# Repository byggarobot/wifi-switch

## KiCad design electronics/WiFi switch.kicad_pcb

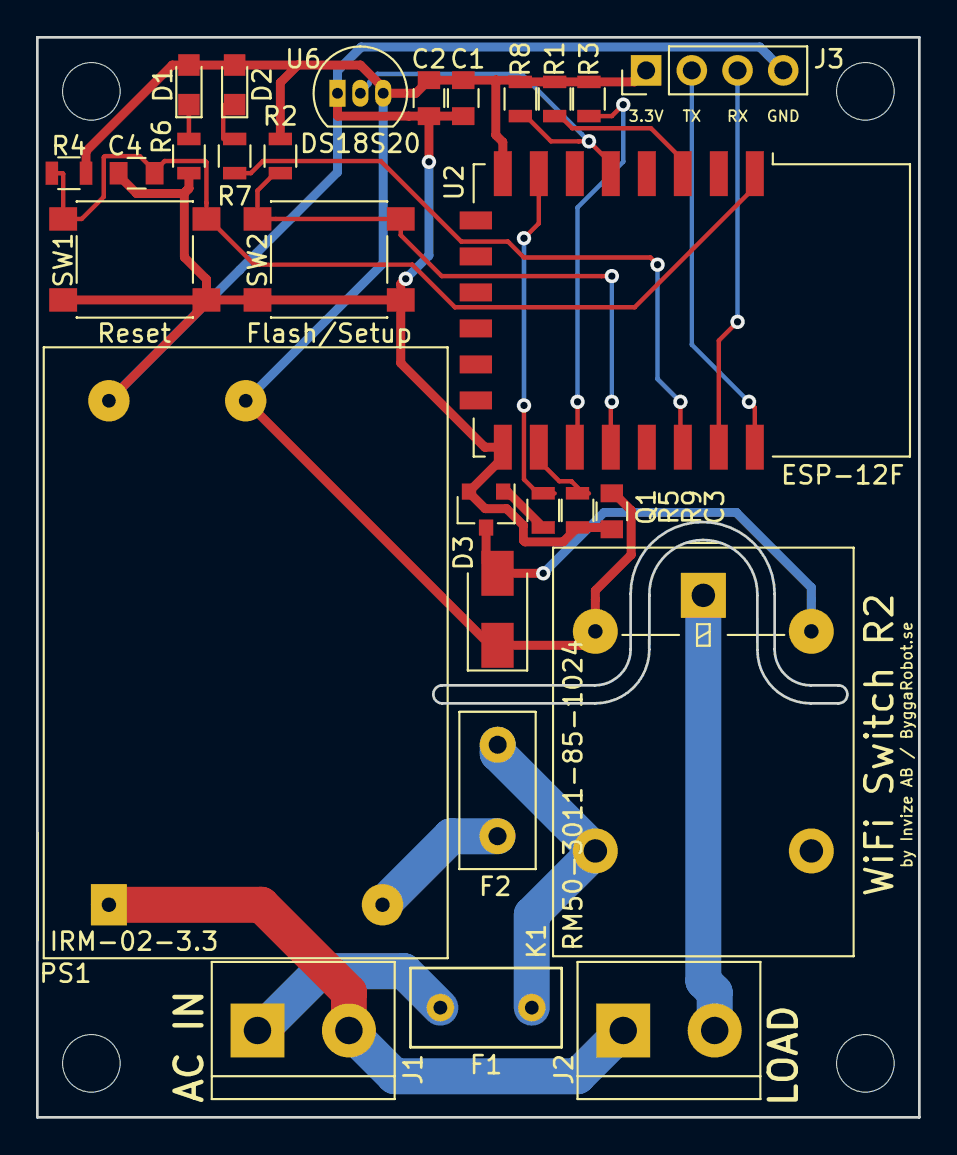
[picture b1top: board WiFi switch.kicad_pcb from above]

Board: 2 copper layers, 49.0 x 60.0 mm, 28 parts (0 on the bottom side), 21 nets.

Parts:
C1, C3: 10uF; C_0805
C2, C4: 100nF; C_0805
D1, D2: LED; LED_0805
D3: SS34; D_SMA
F1: 5A; RS Pro Non-resettable fuse
F2: 0.08A LVR008NK; Fuse_TE5_Littlefuse-395Series
J1: AC IN; TerminalBlock_bornier-2_P5.08mm
J2: LOAD; TerminalBlock_bornier-2_P5.08mm
J3: Programmer; Pin_Header_Straight_1x04_Pitch2.54mm
K1: RM50-3011-85-1024; Relay_SPDT_Relpol_RM50-3011-85-1024
PS1: IRM-02-3.3; ACDC-Conv_THTMeanWell-IRM-02-XX
Q1: BC817; SOT-23
R1, R2, R3, R4, R5, R6, R7: 10K; R_0805
R8: 4.7K; R_0805
R9: 1K; R_0805
SW1: Reset; SW_SPST_PTS645
SW2: Flash/Setup; SW_SPST_PTS645
U2: ESP-12F; ESP-12E
U6: DS18S20; TO-92_Inline_Narrow_Oval

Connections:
+3V3: C1.1, C2.1, C3.1, D1.2, D2.2, D3.1, J3.1, K1.A1, PS1.4, R1.2, R2.2, R3.2, R4.2, R8.2, U2.8, U6.3
/SW-B: J2.2, K1.11
AC-L: F1.1, F2.2, K1.14
AC-N: J1.2, J2.1, PS1.1
D1: R7.1, U2.20
D3: R2.1, SW2.1, U2.18
D4: R3.1, U2.17
D5: R8.1, U2.5, U6.2
D7: R9.2, U2.7
D8: R5.1, U2.16
EN: R1.1, U2.3
GND: C1.2, C2.2, C3.2, C4.2, J3.4, PS1.3, Q1.2, R5.2, R6.1, SW1.2, SW2.2, U2.15, U6.1
unnamed: D1.1, R6.2
unnamed: D2.1, R7.2
unnamed: D3.2, K1.A2, Q1.3
unnamed: F1.2, J1.1
unnamed: F2.1, PS1.2
unnamed: Q1.1, R9.1
RST: C4.1, R4.1, SW1.1, U2.1
RX: J3.3, U2.21
TX: J3.2, U2.22

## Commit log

2019-03-27 First revision
2019-03-27 Add schematics in PDF format
2019-04-01 Update schematics with fuse, reset button and manual flash button
2019-04-01 Update component annotations
2019-04-01 Update PCB for latest schematics changes
2019-04-04 Fix front silk screen layout
